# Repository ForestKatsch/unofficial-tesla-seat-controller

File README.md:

# (unofficial) Tesla seat controller

This project contains everything necessary to build an Arduino shield that reads the seat controls and drives the seat motors and ventilation fans.

## Why?

I built a simracing rig, and I discovered that used Tesla seats in good condition were around the same price as purpose-built simracing seats, and are much more comfortable to boot. The only problem is that they're electrically actuated and can't be manually adjusted.

## How?

- [**Instructions**](docs/instructions.md) (start here)
- [Switchpack reverse-engineering](docs/switchpack.md)

## Changelog

| date       | change                                               |
| ---------- | ---------------------------------------------------- |
| 2025.01.04 | documentation consolidation and prep work for proto1 |
| 2024.08.18 | proto0 / validation                                  |

## References and sources

- [Dan Simma's video](https://www.youtube.com/watch?v=71O_Hcep4HI) convinced me this project was doable
- [Tesla's Model S electrical schematics](https://service.tesla.com/docs/ModelS/ElectricalReference/prog-54/interactive/html/index.html?page=62&) made it easy to find out which wires went where
- [A Delta PWM fan, very similar to the ventilation fans in the seat](https://www.delta-fan.com/applications/automotive/BFB1012HD-04D4L.html)

## License

TODO

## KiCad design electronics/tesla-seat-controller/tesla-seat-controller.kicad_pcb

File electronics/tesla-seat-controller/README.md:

# Standalone Tesla seat controller

STM32G0-based controller for four seat motors, two ventilation fans, and the seat switchpack. Input is a regulated 12 V Mean Well power supply; record the exact model before system testing.

## Design status

The schematic passes ERC and the automated MCU pin-contract tests. The DRV8262s use KiCad's official top-PowerPAD DDV footprint:

`Package_SO:HTSSOP-44_6.1x14mm_P0.635mm_TopEP4.14x7.01mm`

Do not substitute the bottom-PowerPAD DDW footprint. The DDV thermal pad is on top and requires a heatsink for sustained high current.

## PCB requirements

- Put each driver's 10 nF VM capacitors directly at its VM/PGND pin groups.
- Put the VCP, CPH/CPL, DVDD, and VCC capacitors directly at their pins.
- Give both drivers short, wide, comparable +12 V and ground paths; do not feed one through the other.
- Preserve top-side clearance and mounting support for both DRV8262 heatsinks.
- Route motor and input current paths for the fused 10 A system current plus short peaks.
- Clearly label motor outputs A/B/C/D on silkscreen. XT30 polarity marks are not fixed electrical polarity on reversible motor outputs.
- Run DRC and a separate PCB audit before fabrication.

## Firmware safety contract

- DRV8262 hardware current regulation is about 14.6 A nominal; expected motor stall current is about 8 A.
- Monitor IPROPI and stop a motor when an 8 A-class stall persists beyond the chosen timeout.
- Use PWM-mode `00` to coast when stopping. Ramp down before reversing; do not reverse directly at full duty. This limits regeneration into the Mean Well supply.
- Treat nFAULT as latched: clear a fault with the datasheet-defined nSLEEP reset sequence.
- Fan outputs are open-drain and inverted. The Delta reference fan expects approximately 100 Hz PWM and stops near both duty-cycle extremes; validate against the actual seat fans.

## Validation

Run from the repository root:

```sh
kicad-cli sch erc --severity-all --format report \
  --output /tmp/tesla-seat-controller-erc.rpt \
  electronics/tesla-seat-controller/tesla-seat-controller.kicad_sch

python3 tests/test_pinmap.py
```

Before powering motors, verify the exact Mean Well model can supply the expected startup current. During first hardware tests, scope +12 V while stopping and reversing a loaded motor; add a braking clamp only if the rail rises excessively or the supply trips.

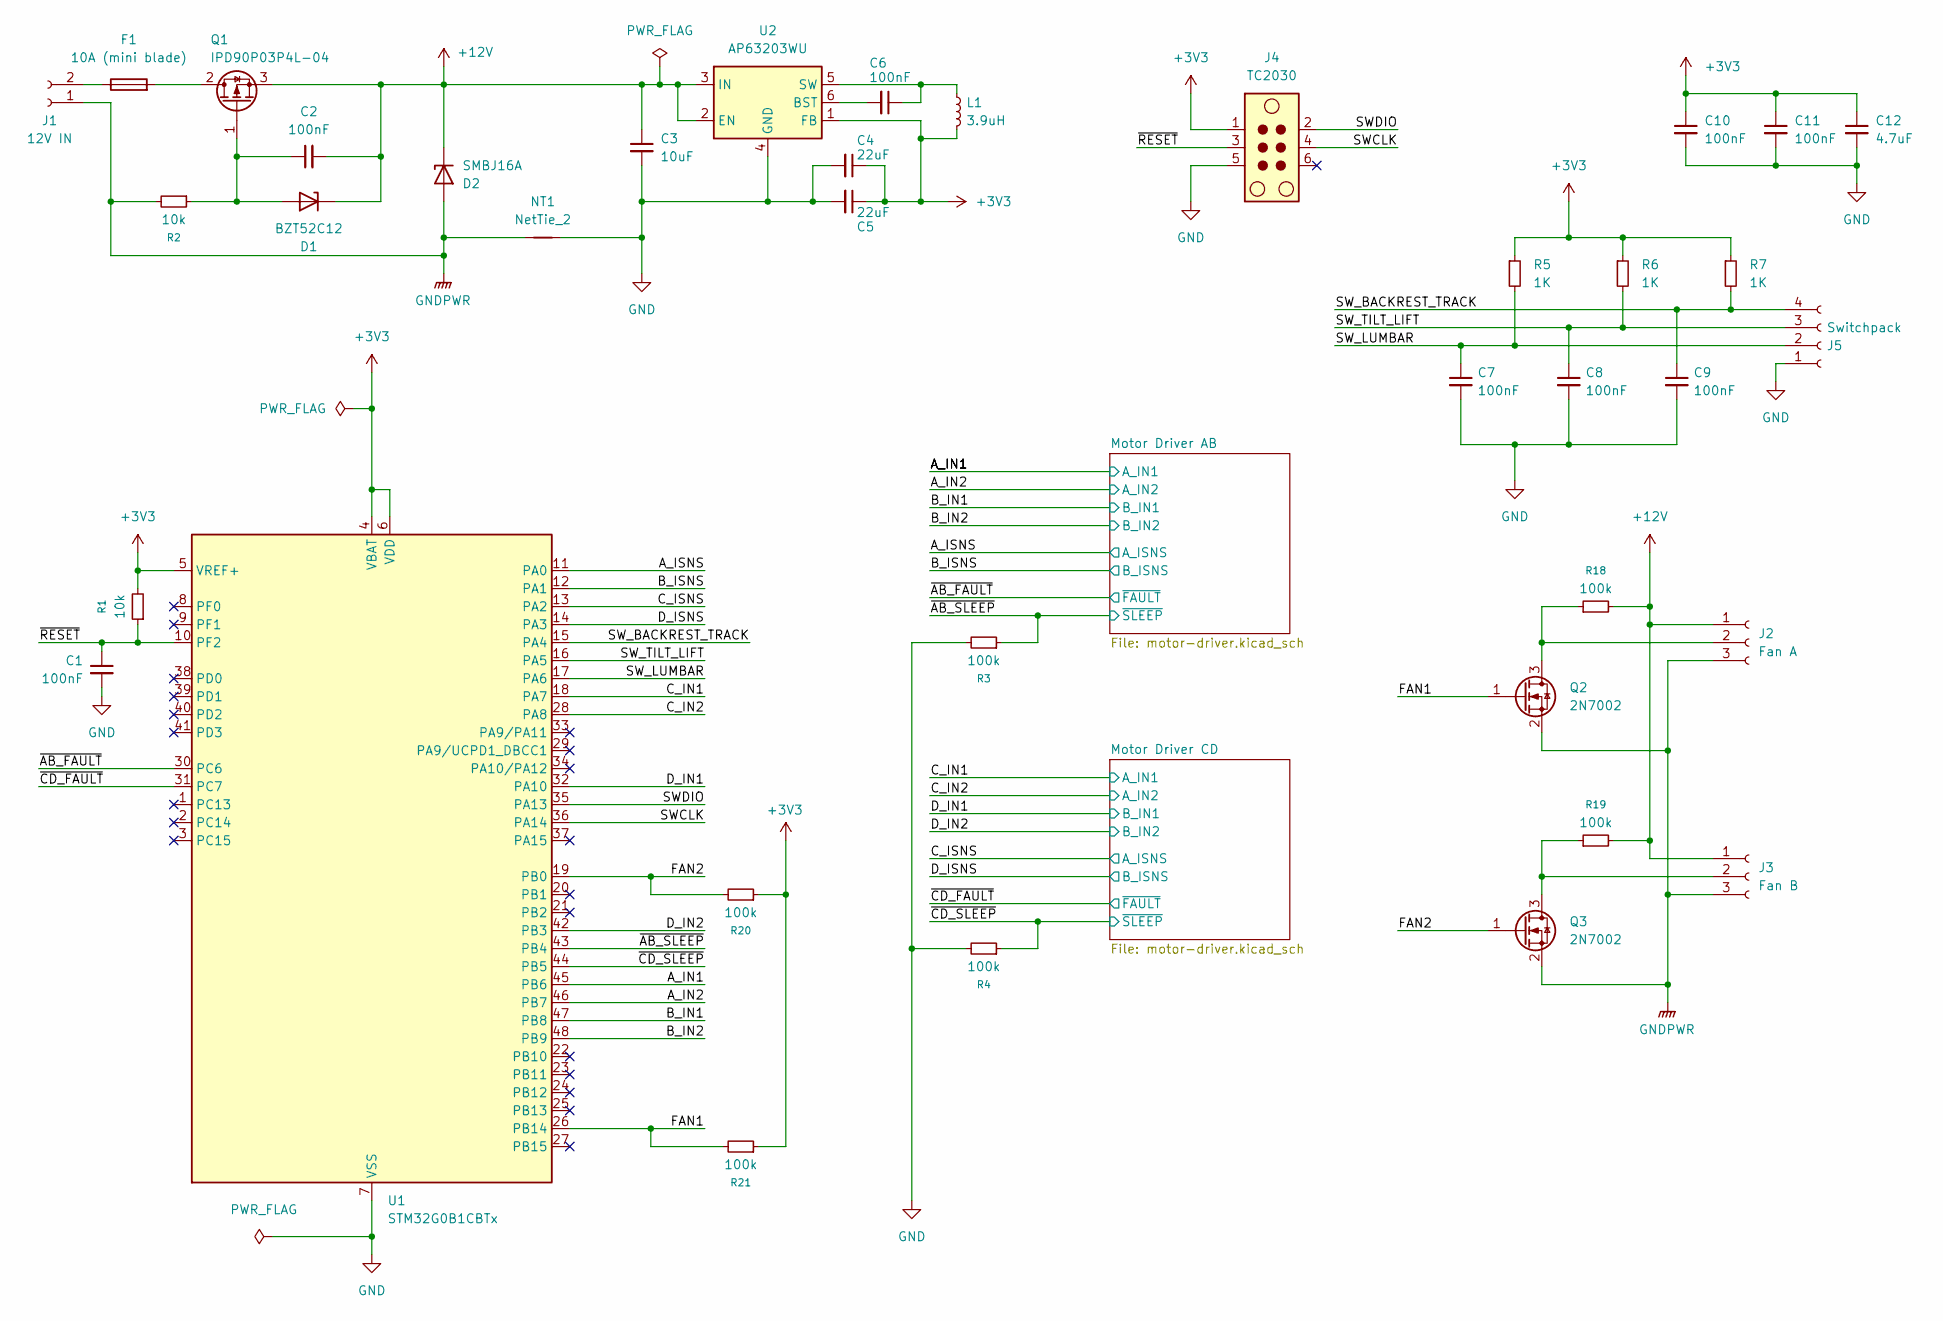
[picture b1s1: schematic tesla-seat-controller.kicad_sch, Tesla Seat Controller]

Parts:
C1, C2, C6, C7, C8, C9, C10, C11: 100nF; C_0805_2012Metric
C3: 10uF; C_1206_3216Metric
C4, C5: 22uF; C_1206_3216Metric
C12: 4.7uF; C_0805_2012Metric
D1: BZT52C12; D_SOD-123
D2: SMBJ16A; D_SMB
F1: 10A (mini blade); Fuseholder_Blade_Mini_Keystone_3568
J1: 12V IN; AMASS_XT30PW-M_1x02_P2.50mm_Horizontal
J2: Fan A; JST_XH_S3B-XH-A_1x03_P2.50mm_Horizontal
J3: Fan B; JST_XH_S3B-XH-A_1x03_P2.50mm_Horizontal
J4: TC2030; Tag-Connect_TC2030-IDC-NL_2x03_P1.27mm_Vertical
J5: Switchpack; JST_XH_S4B-XH-A_1x04_P2.50mm_Horizontal
L1: 3.9uH; L_Bourns_SRN6045TA
NT1: NetTie_2
Q1: IPD90P03P4L-04; TO-252-2
Q2, Q3: 2N7002; SOT-23
R1, R2: 10k; R_0805_2012Metric
R3, R4, R18, R19, R20, R21: 100k; R_0805_2012Metric
R5, R6, R7: 1K; R_0805_2012Metric
U1: STM32G0B1CBTx; LQFP-48_7x7mm_P0.5mm
U2: AP63203WU; TSOT-23-6

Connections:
+3V3: C4.1, C5.1, C10.1, C11.1, C12.1, J4.1, L1.2, R1.2, R5.1, R6.1, R7.1, R20.1, R21.1, U1.4 (VBAT), U1.5 (VREF+), U1.6 (VDD), U2.1 (FB); also elsewhere on the board
+12V: C2.2, C3.1, D1.1 (K), D2.1 (K), J2.1, J3.1, Q1.3 (S), R18.2, R19.2, U2.2 (EN), U2.3 (IN); also elsewhere on the board
/A_IN1: U1.45 (PB6); also elsewhere on the board
/A_IN2: U1.46 (PB7); also elsewhere on the board
/A_ISNS: U1.11 (PA0); also elsewhere on the board
/B_IN1: U1.47 (PB8); also elsewhere on the board
/B_IN2: U1.48 (PB9); also elsewhere on the board
/B_ISNS: U1.12 (PA1); also elsewhere on the board
/C_IN1: U1.18 (PA7); also elsewhere on the board
/C_IN2: U1.28 (PA8); also elsewhere on the board
/C_ISNS: U1.13 (PA2); also elsewhere on the board
/D_IN1: U1.32 (PA10); also elsewhere on the board
/D_IN2: U1.42 (PB3); also elsewhere on the board
/D_ISNS: U1.14 (PA3); also elsewhere on the board
/FAN1: Q2.1 (G), R21.2, U1.26 (PB14)
/FAN2: Q3.1 (G), R20.2, U1.19 (PB0)
/SWCLK: J4.4, U1.36 (PA14)
/SWDIO: J4.2, U1.35 (PA13)
/SW_BACKREST_TRACK: C9.1, J5.4, R7.2, U1.15 (PA4)
/SW_LUMBAR: C7.1, J5.2, R5.2, U1.17 (PA6)
/SW_TILT_LIFT: C8.1, J5.3, R6.2, U1.16 (PA5)
/~AB_FAULT: U1.30 (PC6); also elsewhere on the board
/~AB_SLEEP: R3.1, U1.43 (PB4); also elsewhere on the board
/~CD_FAULT: U1.31 (PC7); also elsewhere on the board
/~CD_SLEEP: R4.1, U1.44 (PB5); also elsewhere on the board
/~RESET: C1.1, J4.3, R1.1, U1.10 (PF2)
GND: C1.2, C3.2, C4.2, C5.2, C7.2, C8.2, C9.2, C10.2, C11.2, C12.2, J4.5, J5.1, NT1.2, R3.2, R4.2, U1.7 (VSS), U2.4 (GND); also elsewhere on the board
GNDPWR: D2.2 (A), J1.1, J2.3, J3.3, NT1.1, Q2.2 (S), Q3.2 (S), R2.2; also elsewhere on the board
unnamed: C2.1, D1.2 (A), Q1.1 (G), R2.1
unnamed: F1.1, J1.2
unnamed: J2.2, Q2.3 (D), R18.1
unnamed: J3.2, Q3.3 (D), R19.1
unnamed: F1.2, Q1.2 (D)
unnamed: C6.2, U2.6 (BST)
unnamed: C6.1, L1.1, U2.5 (SW)

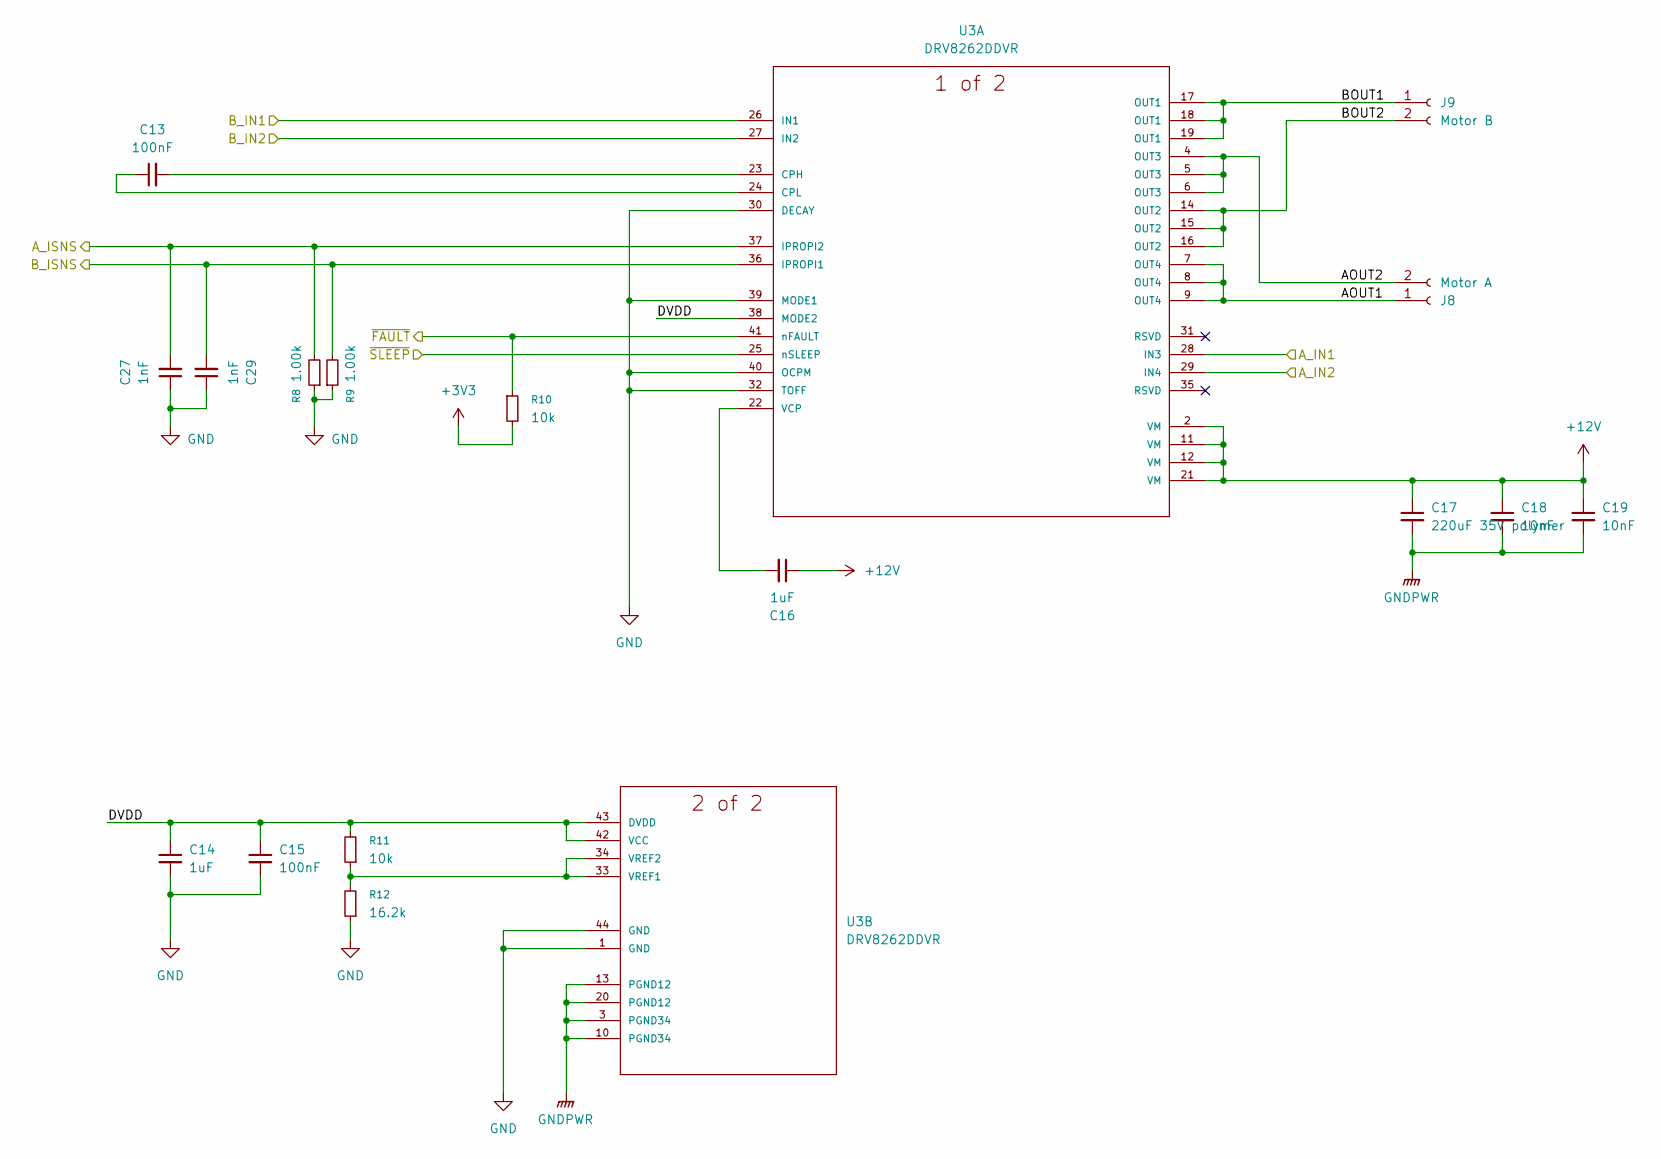
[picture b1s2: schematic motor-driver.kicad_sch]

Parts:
C13, C15: 100nF; C_0805_2012Metric
C14, C16: 1uF; C_0805_2012Metric
C17: 220uF 35V polymer; CP_Elec_10x10.5
C18, C19: 10nF; C_0805_2012Metric
C27, C29: 1nF; C_0805_2012Metric
J8: Motor A; AMASS_XT30PW-F_1x02_P2.50mm_Horizontal
J9: Motor B; AMASS_XT30PW-F_1x02_P2.50mm_Horizontal
R8, R9: 1.00k; R_0805_2012Metric
R10, R11: 10k; R_0805_2012Metric
R12: 16.2k; R_0805_2012Metric
U3: DRV8262DDVR; HTSSOP-44_6.1x14mm_P0.635mm_TopEP4.14x7.01mm; MANUFACTURER_PART_NUMBER DRV8262DDVR

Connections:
+3V3: R10.2; also elsewhere on the board
+12V: C16.1, C17.1, C18.1, C19.1, U3.2 (VM), U3.11 (VM), U3.12 (VM), U3.21 (VM); also elsewhere on the board
/A_IN1: U3.28 (IN3); also elsewhere on the board
/A_IN2: U3.29 (IN4); also elsewhere on the board
/A_ISNS: C27.2, R8.2, U3.37 (IPROPI2); also elsewhere on the board
/B_IN1: U3.26 (IN1); also elsewhere on the board
/B_IN2: U3.27 (IN2); also elsewhere on the board
/B_ISNS: C29.2, R9.2, U3.36 (IPROPI1); also elsewhere on the board
/Motor Driver AB/AOUT1: J8.1, U3.7 (OUT4), U3.8 (OUT4), U3.9 (OUT4)
/Motor Driver AB/AOUT2: J8.2, U3.4 (OUT3), U3.5 (OUT3), U3.6 (OUT3)
/Motor Driver AB/BOUT1: J9.1, U3.17 (OUT1), U3.18 (OUT1), U3.19 (OUT1)
/Motor Driver AB/BOUT2: J9.2, U3.14 (OUT2), U3.15 (OUT2), U3.16 (OUT2)
/Motor Driver AB/DVDD: C14.1, C15.1, R11.2, U3.38 (MODE2), U3.42 (VCC), U3.43 (DVDD)
/~AB_FAULT: R10.1, U3.41 (nFAULT); also elsewhere on the board
/~AB_SLEEP: U3.25 (nSLEEP); also elsewhere on the board
GND: C14.2, C15.2, C27.1, C29.1, R8.1, R9.1, R12.1, U3.1 (GND), U3.30 (DECAY), U3.32 (TOFF), U3.39 (MODE1), U3.40 (OCPM), U3.44 (GND); also elsewhere on the board
GNDPWR: C17.2, C18.2, C19.2, U3.3 (PGND34), U3.10 (PGND34), U3.13 (PGND12), U3.20 (PGND12); also elsewhere on the board
unnamed: C13.2, U3.23 (CPH)
unnamed: C13.1, U3.24 (CPL)
unnamed: C16.2, U3.22 (VCP)
unnamed: R11.1, R12.2, U3.33 (VREF1), U3.34 (VREF2)

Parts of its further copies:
C20, C22: 100nF; C_0805_2012Metric
C21, C23: 1uF; C_0805_2012Metric
C24: 220uF 35V polymer; CP_Elec_10x10.5
C25, C26: 10nF; C_0805_2012Metric
C28, C30: 1nF; C_0805_2012Metric
J6: Motor A; AMASS_XT30PW-F_1x02_P2.50mm_Horizontal
J7: Motor B; AMASS_XT30PW-F_1x02_P2.50mm_Horizontal
R13, R14: 1.00k; R_0805_2012Metric
R15, R16: 10k; R_0805_2012Metric
R17: 16.2k; R_0805_2012Metric
U4: DRV8262DDVR; HTSSOP-44_6.1x14mm_P0.635mm_TopEP4.14x7.01mm; MANUFACTURER_PART_NUMBER DRV8262DDVR

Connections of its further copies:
+3V3: R15.2; also elsewhere on the board
+12V: C23.1, C24.1, C25.1, C26.1, U4.2 (VM), U4.11 (VM), U4.12 (VM), U4.21 (VM); also elsewhere on the board
/C_IN1: U4.28 (IN3); also elsewhere on the board
/C_IN2: U4.29 (IN4); also elsewhere on the board
/C_ISNS: C28.2, R13.2, U4.37 (IPROPI2); also elsewhere on the board
/D_IN1: U4.26 (IN1); also elsewhere on the board
/D_IN2: U4.27 (IN2); also elsewhere on the board
/D_ISNS: C30.2, R14.2, U4.36 (IPROPI1); also elsewhere on the board
/Motor Driver CD/AOUT1: J6.1, U4.7 (OUT4), U4.8 (OUT4), U4.9 (OUT4)
/Motor Driver CD/AOUT2: J6.2, U4.4 (OUT3), U4.5 (OUT3), U4.6 (OUT3)
/Motor Driver CD/BOUT1: J7.1, U4.17 (OUT1), U4.18 (OUT1), U4.19 (OUT1)
/Motor Driver CD/BOUT2: J7.2, U4.14 (OUT2), U4.15 (OUT2), U4.16 (OUT2)
/Motor Driver CD/DVDD: C21.1, C22.1, R16.2, U4.38 (MODE2), U4.42 (VCC), U4.43 (DVDD)
/~CD_FAULT: R15.1, U4.41 (nFAULT); also elsewhere on the board
/~CD_SLEEP: U4.25 (nSLEEP); also elsewhere on the board
GND: C21.2, C22.2, C28.1, C30.1, R13.1, R14.1, R17.1, U4.1 (GND), U4.30 (DECAY), U4.32 (TOFF), U4.39 (MODE1), U4.40 (OCPM), U4.44 (GND); also elsewhere on the board
GNDPWR: C24.2, C25.2, C26.2, U4.3 (PGND34), U4.10 (PGND34), U4.13 (PGND12), U4.20 (PGND12); also elsewhere on the board
unnamed: C20.2, U4.23 (CPH)
unnamed: C20.1, U4.24 (CPL)
unnamed: C23.2, U4.22 (VCP)
unnamed: R16.1, R17.2, U4.33 (VREF1), U4.34 (VREF2)

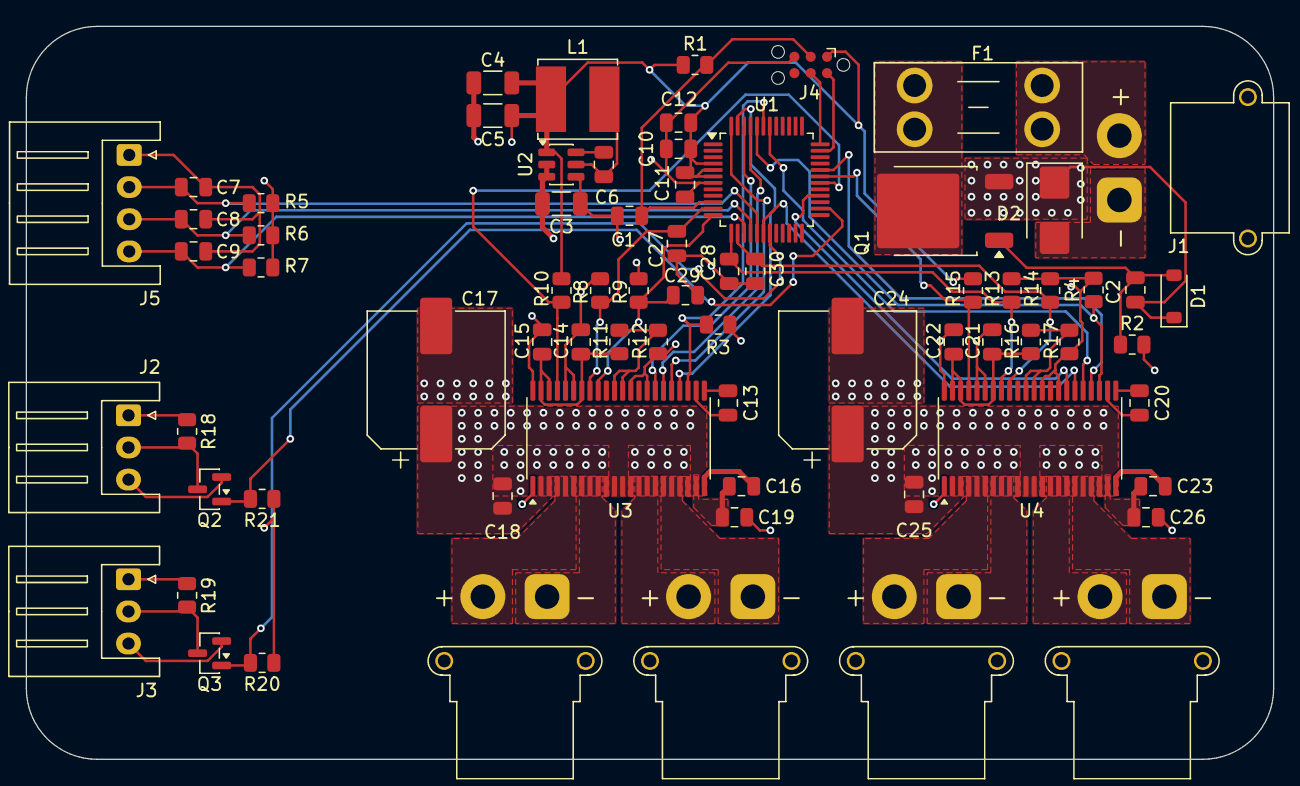
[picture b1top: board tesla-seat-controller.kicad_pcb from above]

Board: 4 copper layers, 97.0 x 57.0 mm, 71 parts (0 on the bottom side), 53 nets.

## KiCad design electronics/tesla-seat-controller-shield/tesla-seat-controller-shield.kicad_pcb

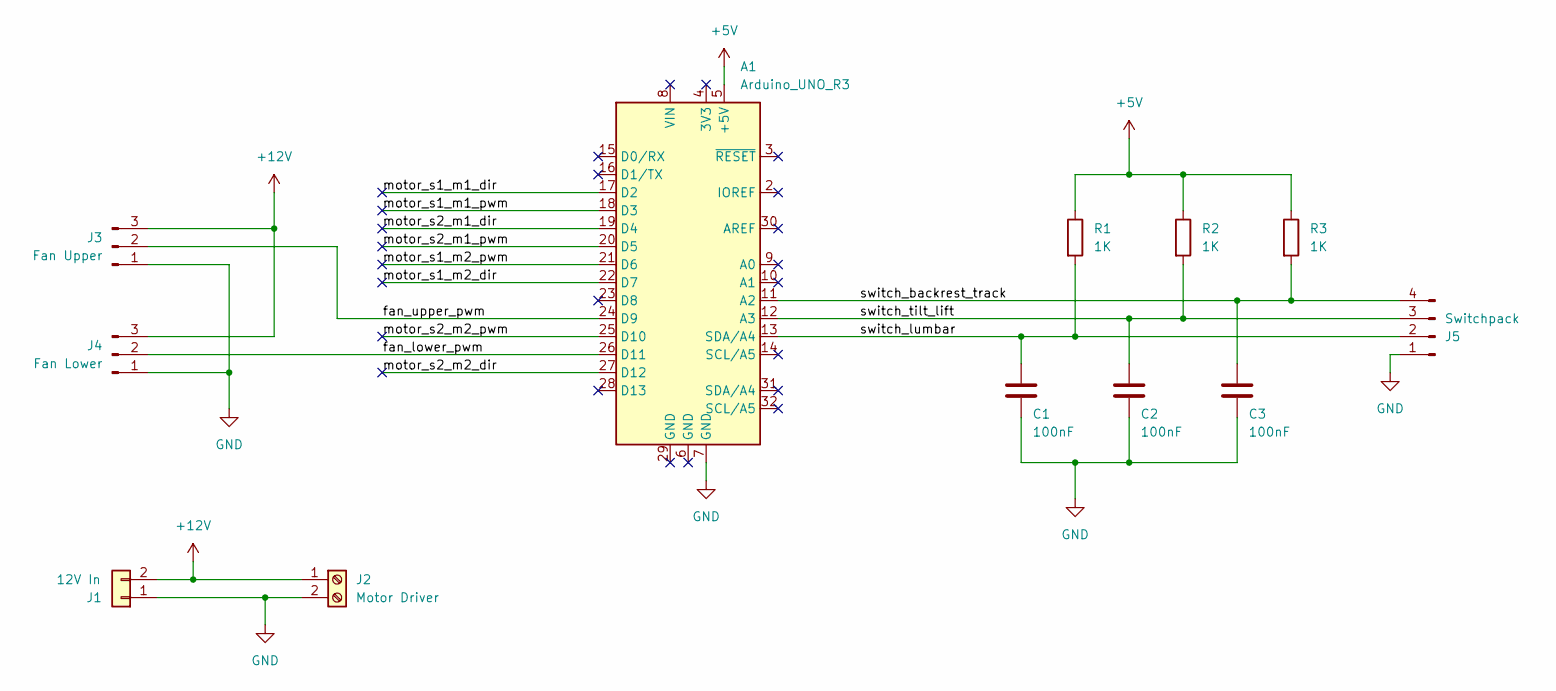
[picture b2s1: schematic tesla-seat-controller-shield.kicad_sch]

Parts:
A1: Arduino_UNO_R3
C1, C2, C3: 100nF; C_0805_2012Metric_Pad1.18x1.45mm_HandSolder
J1: 12V In; AMASS_XT30PW-M_1x02_P2.50mm_Horizontal
J2: Motor Driver; TerminalBlock_bornier-2_P5.08mm
J3: Fan Upper; PinHeader_1x03_P2.54mm_Vertical
J4: Fan Lower; PinHeader_1x03_P2.54mm_Vertical
J5: Switchpack; PinHeader_1x04_P2.54mm_Vertical
R1, R2, R3: 1K; R_0805_2012Metric_Pad1.20x1.40mm_HandSolder

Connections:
+5V: A1.5 (+5V), R1.1, R2.1, R3.1
+12V: J1.2, J2.1, J3.3, J4.3
/fan_lower_pwm: A1.26 (D11), J4.2
/fan_upper_pwm: A1.24 (D9), J3.2
/motor_s1_m1_dir: A1.17 (D2)
/motor_s1_m1_pwm: A1.18 (D3)
/motor_s1_m2_dir: A1.22 (D7)
/motor_s1_m2_pwm: A1.21 (D6)
/motor_s2_m1_dir: A1.19 (D4)
/motor_s2_m1_pwm: A1.20 (D5)
/motor_s2_m2_dir: A1.27 (D12)
/motor_s2_m2_pwm: A1.25 (D10)
/switch_backrest_track: A1.11 (A2), C3.1, J5.4, R3.2
/switch_lumbar: A1.13 (SDA/A4), C1.1, J5.2, R1.2
/switch_tilt_lift: A1.12 (A3), C2.1, J5.3, R2.2
GND: A1.7 (GND), C1.2, C2.2, C3.2, J1.1, J2.2, J3.1, J4.1, J5.1

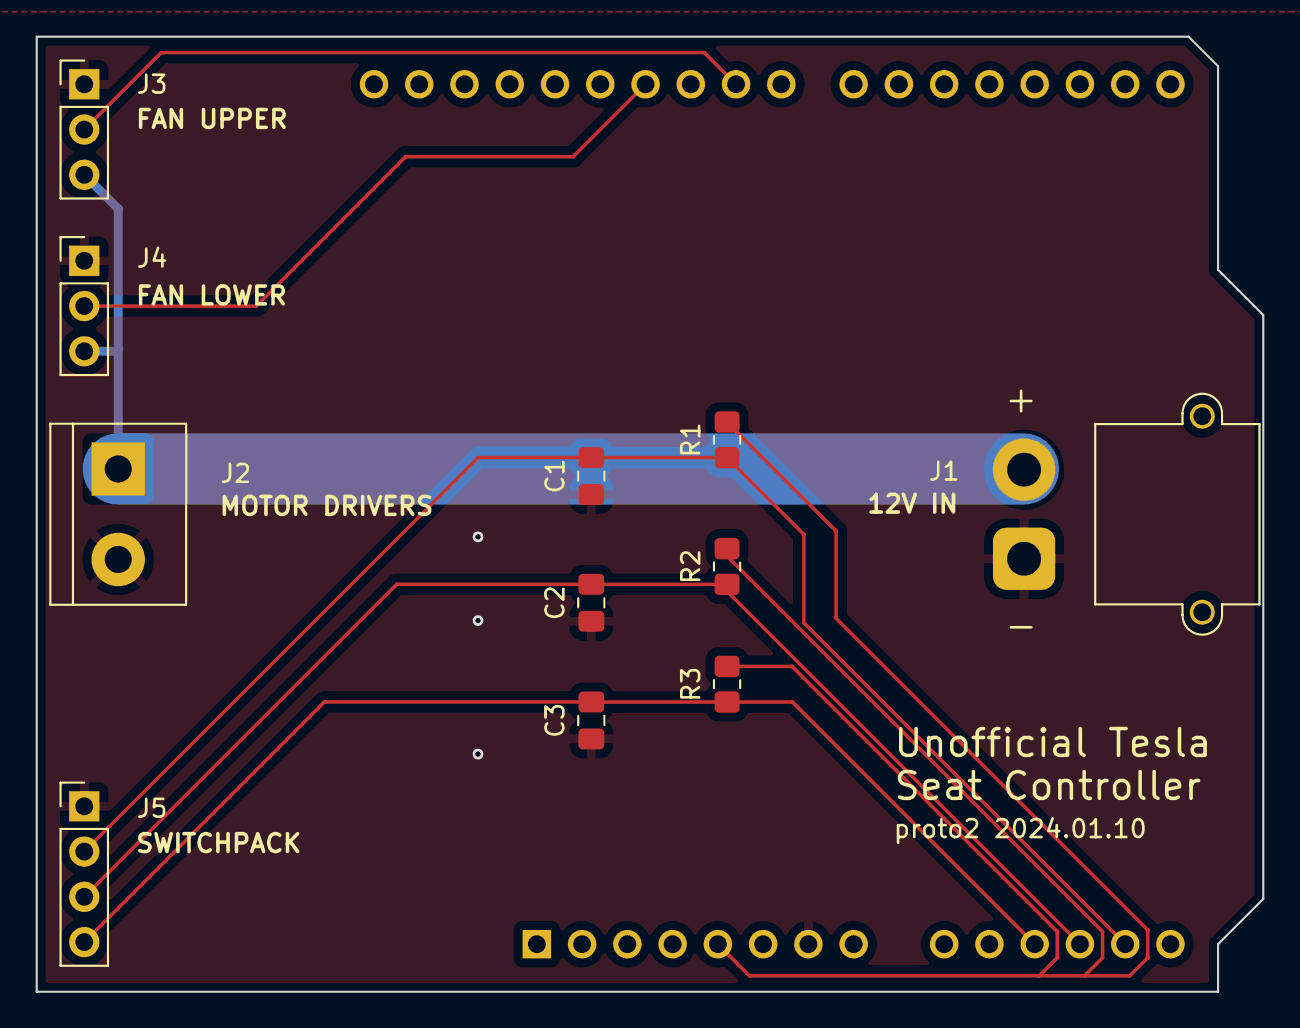
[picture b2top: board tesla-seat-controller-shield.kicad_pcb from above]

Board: 11 copper layers, 68.8 x 53.6 mm, 12 parts (1 on the bottom side), 8 nets.

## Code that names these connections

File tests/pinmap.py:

"""Pin assignment contract for the standalone (shieldless) seat controller.

This is the single source of truth for how firmware is allowed to use the
STM32G0B1CBTx (LQFP-48, U1) on the standalone board. Values are hand-copied
from two authoritative sources:

  * net / pin assignments: electronics/tesla-seat-controller/tesla-seat-controller.kicad_sch
    (validated automatically against a fresh netlist export by test_pinmap.py)
  * timer / ADC capabilities: STM32G0B1xB/xC/xE datasheet DS13560 Rev 6,
    Tables 13-16 (alternate functions) and Table 12 (pin definitions)

Rules encoded here (enforced by test_pinmap.py):
  - every PWM signal must name a real (timer, channel, AF) that exists on
    that pin per the datasheet;
  - no timer channel may be claimed twice;
  - a channel and its complementary output (CHx vs CHxN) may not both be
    claimed - they are one output stage on advanced timers, not two PWMs;
  - ADC signals must name the correct ADC_INx channel for the pin;
  - ISNS inputs must sit on 5 V-tolerant (FT) pins because the DRV8262
    clamps IPROPI near VREF (~3.3 V) and overshoot must not kill the pin;
  - both inputs of one motor should share a timer (same counter -> identical
    frequency/phase). Motor C is a documented exception, see below.

Timer budget (firmware must configure all PWM timers to the same base
frequency where a motor spans two timers):
  TIM4  -> motor A (CH1/CH2) and motor B (CH3/CH4)
  TIM1  -> motor C low side (CH1) and motor D (CH2/CH3)  [advanced timer: set MOE]
  TIM14 -> motor C high side (CH1). PA7 has no plain TIM1 channel - its only
           TIM1 option is CH1N, the complement of PA8's CH1, so motor C is
           deliberately split across TIM1 + TIM14 (keep both at one frequency).
  TIM15 -> fan 1 (CH1)  [advanced-ish: set MOE]
  TIM3  -> fan 2 (CH3), frequency independent of all motor timers
"""

# role: 'pwm' | 'adc' | 'gpio_in' | 'gpio_out' | 'swd'
# pwm fields:  timer, ch, comp (True = complementary CHxN output), af
# adc fields:  adc_ch (ADC_INx)
PINMAP = {
    # DRV8262 U3 ("AB"), PWM inputs
    "A_IN1": dict(pin="PB6",  net="/A_IN1",  role="pwm", timer="TIM4",  ch=1, comp=False, af=9),
    "A_IN2": dict(pin="PB7",  net="/A_IN2",  role="pwm", timer="TIM4",  ch=2, comp=False, af=9),
    "B_IN1": dict(pin="PB8",  net="/B_IN1",  role="pwm", timer="TIM4",  ch=3, comp=False, af=9),
    "B_IN2": dict(pin="PB9",  net="/B_IN2",  role="pwm", timer="TIM4",  ch=4, comp=False, af=9),

    # DRV8262 U4 ("CD"), PWM inputs
    "C_IN1": dict(pin="PA7",  net="/C_IN1",  role="pwm", timer="TIM14", ch=1, comp=False, af=4),
    "C_IN2": dict(pin="PA8",  net="/C_IN2",  role="pwm", timer="TIM1",  ch=1, comp=False, af=2),
    "D_IN1": dict(pin="PA10", net="/D_IN1",  role="pwm", timer="TIM1",  ch=3, comp=False, af=2),
    "D_IN2": dict(pin="PB3",  net="/D_IN2",  role="pwm", timer="TIM1",  ch=2, comp=False, af=1),

    # Fan gate drives (2N7002 gates)
    "FAN1":  dict(pin="PB14", net="/FAN1",   role="pwm", timer="TIM15", ch=1, comp=False, af=5),
    "FAN2":  dict(pin="PB0",  net="/FAN2",   role="pwm", timer="TIM3",  ch=3, comp=False, af=1),

    # DRV8262 current sense (IPROPI, 212 mV/A with R_IPROPI = 1.00k)
    "A_ISNS": dict(pin="PA0", net="/A_ISNS", role="adc", adc_ch=0),
    "B_ISNS": dict(pin="PA1", net="/B_ISNS", role="adc", adc_ch=1),
    "C_ISNS": dict(pin="PA2", net="/C_ISNS", role="adc", adc_ch=2),
    "D_ISNS": dict(pin="PA3", net="/D_ISNS", role="adc", adc_ch=3),

    # Switchpack analog ladder inputs (1k pull-up to 3V3 on board)
    "SW_BACKREST_TRACK": dict(pin="PA4", net="/SW_BACKREST_TRACK", role="adc", adc_ch=4),
    "SW_TILT_LIFT":      dict(pin="PA5", net="/SW_TILT_LIFT",      role="adc", adc_ch=5),
    "SW_LUMBAR":         dict(pin="PA6", net="/SW_LUMBAR",         role="adc", adc_ch=6),

    # DRV8262 control / status
    "AB_SLEEP": dict(pin="PB4", net="/~{AB_SLEEP}", role="gpio_out"),
    "CD_SLEEP": dict(pin="PB5", net="/~{CD_SLEEP}", role="gpio_out"),
    "AB_FAULT": dict(pin="PC6", net="/~{AB_FAULT}", role="gpio_in"),   # open-drain, 10k pull-up on board
    "CD_FAULT": dict(pin="PC7", net="/~{CD_FAULT}", role="gpio_in"),   # open-drain, 10k pull-up on board

    # Debug
    "SWDIO": dict(pin="PA13", net="/SWDIO", role="swd"),
    "SWCLK": dict(pin="PA14", net="/SWCLK", role="swd"),
}

# Motor -> (high-side input, low-side input). Both pins must be PWM-capable;
# pairs listed in SPLIT_TIMER_OK are allowed to span two timers.
MOTOR_PAIRS = {
    "A": ("A_IN1", "A_IN2"),
    "B": ("B_IN1", "B_IN2"),
    "C": ("C_IN1", "C_IN2"),
    "D": ("D_IN1", "D_IN2"),
}
SPLIT_TIMER_OK = {"C"}  # PA7 has no non-complementary TIM1 channel (see module docstring)

# U1 nets that are intentionally not firmware signals.
NON_GPIO_NETS = {"+3V3", "GND", "/~{RESET}"}

# ---------------------------------------------------------------------------
# Datasheet reference data - STM32G0B1xB/xC/xE, DS13560 Rev 6.
# Only the pins this project uses are listed. (pin) -> {(timer, ch, comp): af}
# from Tables 13/14 (port A) and 15/16 (port B).
AF_PWM = {
    "PA7":  {("TIM3", 2, False): 1, ("TIM1", 1, True): 2, ("TIM14", 1, False): 4, ("TIM17", 1, False): 5},
    "PA8":  {("TIM1", 1, False): 2},
    "PA10": {("TIM1", 3, False): 2},
    "PB0":  {("TIM3", 3, False): 1, ("TIM1", 2, True): 2},
    "PB3":  {("TIM1", 2, False): 1, ("TIM2", 2, False): 2},
    "PB6":  {("TIM1", 3, False): 1, ("TIM16", 1, True): 2, ("TIM4", 1, False): 9},
    "PB7":  {("TIM17", 1, True): 2, ("TIM4", 2, False): 9},
    "PB8":  {("TIM16", 1, False): 2, ("TIM4", 3, False): 9},
    "PB9":  {("TIM17", 1, False): 2, ("TIM4", 4, False): 9},
    "PB14": {("TIM1", 2, True): 2, ("TIM15", 1, False): 5},
}

# ADC_INx channel per pin (Table 12).
ADC_CHANNELS = {
    "PA0": 0, "PA1": 1, "PA2": 2, "PA3": 3, "PA4": 4, "PA5": 5, "PA6": 6, "PA7": 7,
}

# I/O structure per pin (Table 12): FT* = 5 V tolerant, TT* = 3.6 V max.
IO_STRUCTURE = {
    "PA0": "FT_a", "PA1": "FT_ea", "PA2": "FT_a", "PA3": "FT_ea",
    "PA4": "TT_a", "PA5": "TT_ea", "PA6": "FT_ea", "PA7": "FT_a",
}

# Signals that must be on 5 V-tolerant pins (DRV8262 IPROPI clamps near
# VREF ~3.3 V; tolerance stack can exceed a TT pin's 3.6 V abs max margin).
REQUIRE_5V_TOLERANT = {"A_ISNS", "B_ISNS", "C_ISNS", "D_ISNS"}

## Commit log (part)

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2025-01-04 first commit; basic docs
2025-01-05 Update switchpack docs
2025-01-05 Add KiCAD PCB
2025-01-05 Mirror Arduino shield and update some documentation paths
2025-01-05 Replace silly vertical mirror with flip + 180
2025-01-10 Add teardrops
2025-01-11 Add 3D models and make board updates to match shield layout
2025-01-11 Update part positions and remove 12v Vin
2025-01-26 Git ignore plots
2025-02-01 Upgrade to KiCAD 9.0.0 rc2
2025-03-16 Reshuffle pins
2025-03-16 Copy in firmware
2025-03-16 Add draft fan support
2025-05-17 kicad 9
2026-06-18 update schematic for 2354
2026-06-20 Finish out protection + fan

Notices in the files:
parts and their libraries:
COPYRIGHT: Copyright (C) 2023 Ultra Librarian. All rights reserved.
